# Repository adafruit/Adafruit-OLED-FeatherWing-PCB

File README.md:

## Adafruit FeatherWing OLED - 128x32 and 128x64 OLED Add-on For Feather PCB
<a href="http://www.adafruit.com/products/2900"><br/>
<a href="http://www.adafruit.com/products/2900"><br/>
Click here to purchase one from the Adafruit shop</a>

PCB files for the Adafruit FeatherWing OLED - 128x32 OLED Add-on For Feather. Format is EagleCAD schematic and board layout
* https://www.adafruit.com/product/2900

and for Adafruit FeatherWing OLED - 128x64 OLED Add-on For Feather - STEMMA QT / Qwiic
* https://www.adafruit.com/product/4650

### Description

A Feather board without ambition is a Feather board without FeatherWings! This is the **FeatherWing OLED**: it adds a 128x32 or 128x64 monochrome OLED plus 3 user buttons to any Feather main board. Using our [Feather Stacking Headers](https://www.adafruit.com/products/2830) or [Feather Female Headers](http://www.adafruit.com/products/2886) you can connect a FeatherWing on top of your Feather board and let the board take flight!

These displays are small, only about 1"-1.3" diagonal, but very readable due to the high contrast of an OLED display. This screen is made of 128x32 individual white OLED pixels and because the display makes its own light, no backlight is required. This reduces the power required to run the OLED and is why the display has such high contrast; we really like this miniature display for its crispness! We also toss on a reset button and three mini tactile buttons called A B and C so you can add a mini user interface to your feather.

The 128x64 display is an SH1107, which uses only I2C so you can easily connect it up with just two pins used (plus power and ground!).  There's an auto-reset circuit and a reset button on the top. We've even included a SparkFun qwiic-compatible STEMMA QT connector for the I2C bus so you can plug and play any of our STEMMA QT, qwiic or Grove I2C sensors and devices!

Tested working with **all Feather boards**. The OLED uses only the two I2C pins on the Feather, and you can pretty much stack it with any other FeatherWing, even ones that use I2C since that is a shared bus. To use, [Check out our tutorial ! It has schematics, datasheets, files, and code examples.](https://learn.adafruit.com/adafruit-oled-featherwing/download)

[Check out our range of Feather boards here.](https://www.adafruit.com/feather)

### License

Adafruit invests time and resources providing this open source design, please support Adafruit and open-source hardware by purchasing products from [Adafruit](https://www.adafruit.com)!

Designed by Limor Fried/Ladyada for Adafruit Industries.

Creative Commons Attribution/Share-Alike, all text above must be included in any redistribution. See license.txt for additional details.

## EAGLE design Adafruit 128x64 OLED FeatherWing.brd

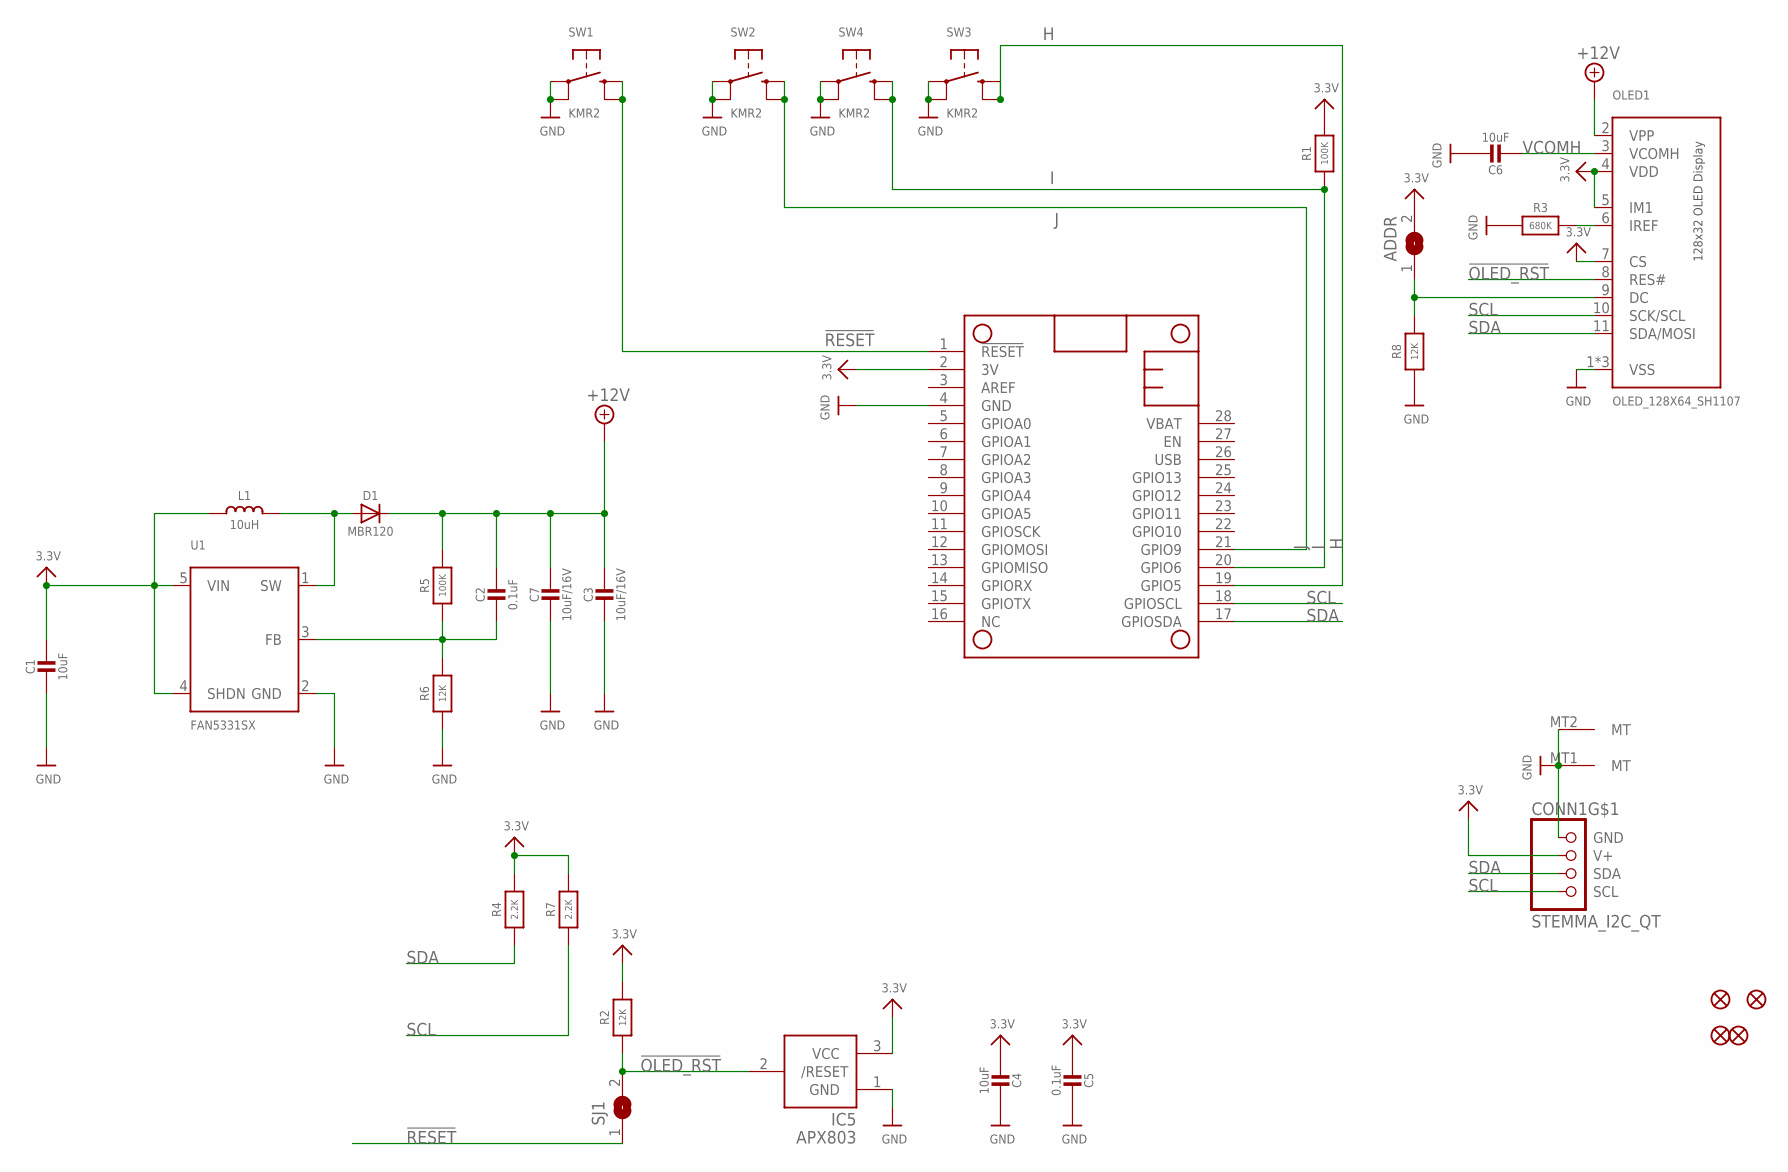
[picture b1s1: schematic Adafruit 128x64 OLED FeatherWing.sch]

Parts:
ADDR: SOLDERJUMPER; SOLDERJUMPER_ARROW_NOPASTE
C1, C4, C6: 10uF; 0805-NO
C2, C5: 0.1uF; 0603-NO
C3, C7: 10uF/16V; 0805-NO
CONN1: STEMMA_I2C_QT; JST_SH4
D1: MBR120; SOD-123
FID1, FID2, FID3, FID4: FIDUCIAL_1MM
IC5: APX803; SOT23
L1: 10uH; INDUCTOR_1007
MS1: FEATHERWING_NODIM
OLED1: OLED_128X64_SH1107; QT1107P11A
R1, R5: 100K; 0603-NO
R2, R6, R8: 12K; 0603-NO
R3: 680K; 0603-NO
R4, R7: 2.2K; 0603-NO
SJ1: SOLDERJUMPERCLOSED; SOLDERJUMPER_CLOSEDWIRE
SW1, SW2, SW3, SW4: KMR2; BTN_KMR2_4.6X2.8
U1: FAN5331SX; SOT23-5

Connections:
3.3V: ADDR.2, C1.1, C4.2, C5.2, CONN1.2 (V+), IC5.3 (VCC), L1.P$1 (1), MS1.2 (3V), OLED1.4 (VDD), OLED1.5 (IM1), OLED1.7 (CS), R1.2, R2.2, R4.2, R7.2, U1.4 (SHDN), U1.5 (VIN)
!OLED_RST: IC5.2 (/RESET), OLED1.8 (RES#), R2.1, SJ1.2
!RESET: MS1.1 (!RESET), SJ1.1, SW1.B (S), SW1.B' (S1)
+12V: C2.1, C3.1, C7.1, D1.C, OLED1.2 (VPP), R5.2
GND: C1.2, C3.2, C4.1, C5.1, C6.1, C7.2, CONN1.1 (GND), CONN1.MT1 (MT), CONN1.MT2 (MT), IC5.1 (GND), MS1.4 (GND), OLED1.1 (VSS), OLED1.12 (VSS), OLED1.13 (VSS), R3.1, R6.1, R8.1, SW1.A, SW1.A' (P1), SW2.A, SW2.A' (P1), SW3.A, SW3.A' (P1), SW4.A, SW4.A' (P1), U1.2 (GND)
H: MS1.19 (GPIO5), SW3.B (S), SW3.B' (S1)
I: MS1.20 (GPIO6), R1.1, SW4.B (S), SW4.B' (S1)
J: MS1.21 (GPIO9), SW2.B (S), SW2.B' (S1)
unnamed: D1.A, L1.P$2 (2), U1.1 (SW)
unnamed: ADDR.1, OLED1.9 (DC), R8.2
unnamed: C2.2, R5.1, R6.2, U1.3 (FB)
unnamed: OLED1.6 (IREF), R3.2
SCL: CONN1.4 (SCL), MS1.18 (GPIOSCL), OLED1.10 (SCK/SCL), R7.1
SDA: CONN1.3 (SDA), MS1.17 (GPIOSDA), OLED1.11 (SDA/MOSI), R4.1
VCOMH: C6.2, OLED1.3 (VCOMH)

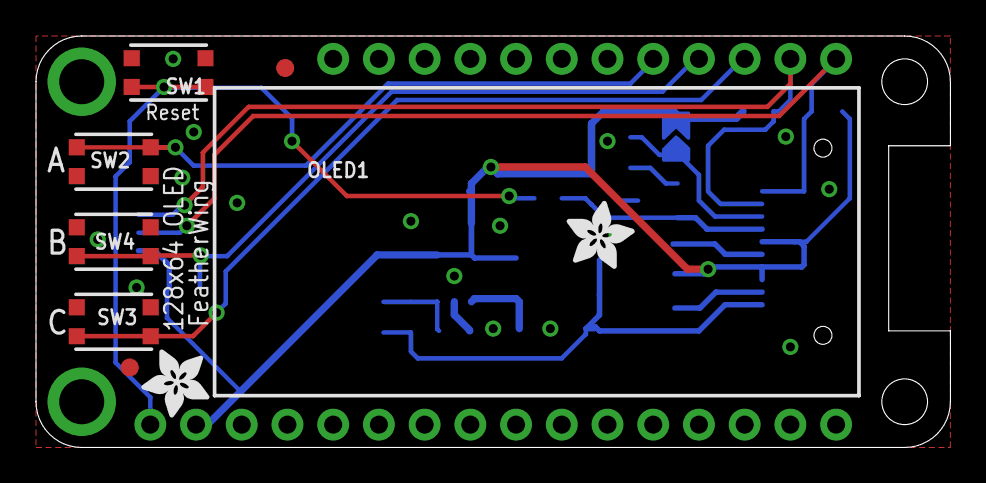
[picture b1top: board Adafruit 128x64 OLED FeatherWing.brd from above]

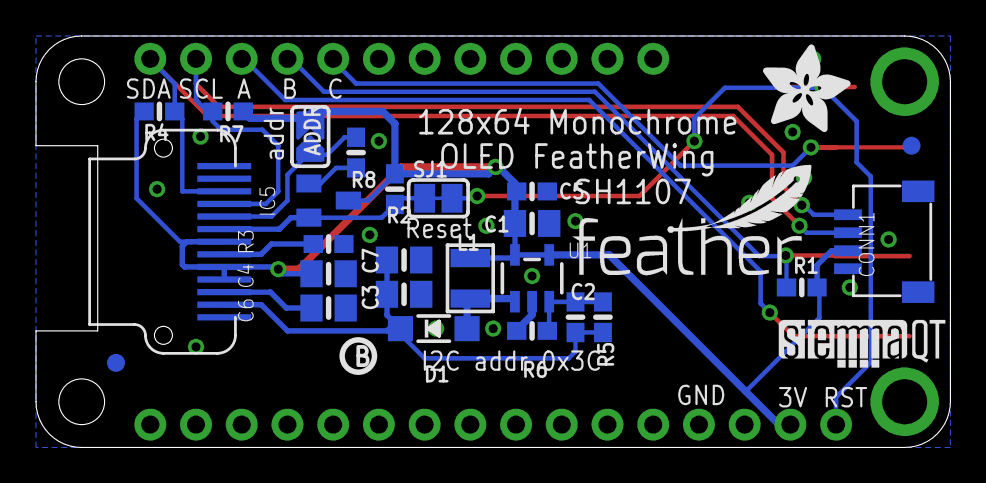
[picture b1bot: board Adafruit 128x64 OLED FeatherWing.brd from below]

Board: 2 copper layers, 50.8 x 22.9 mm, 38 parts (28 on the bottom side), 15 nets.

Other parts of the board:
U$8: ADAFRUIT_5MM
U$14: PCBFEAT-REV-040
U$16, U$37: ADAFRUIT_3.5MM
U$35: STEMMAQT
U$36: FEATHERLOGO_SMALL

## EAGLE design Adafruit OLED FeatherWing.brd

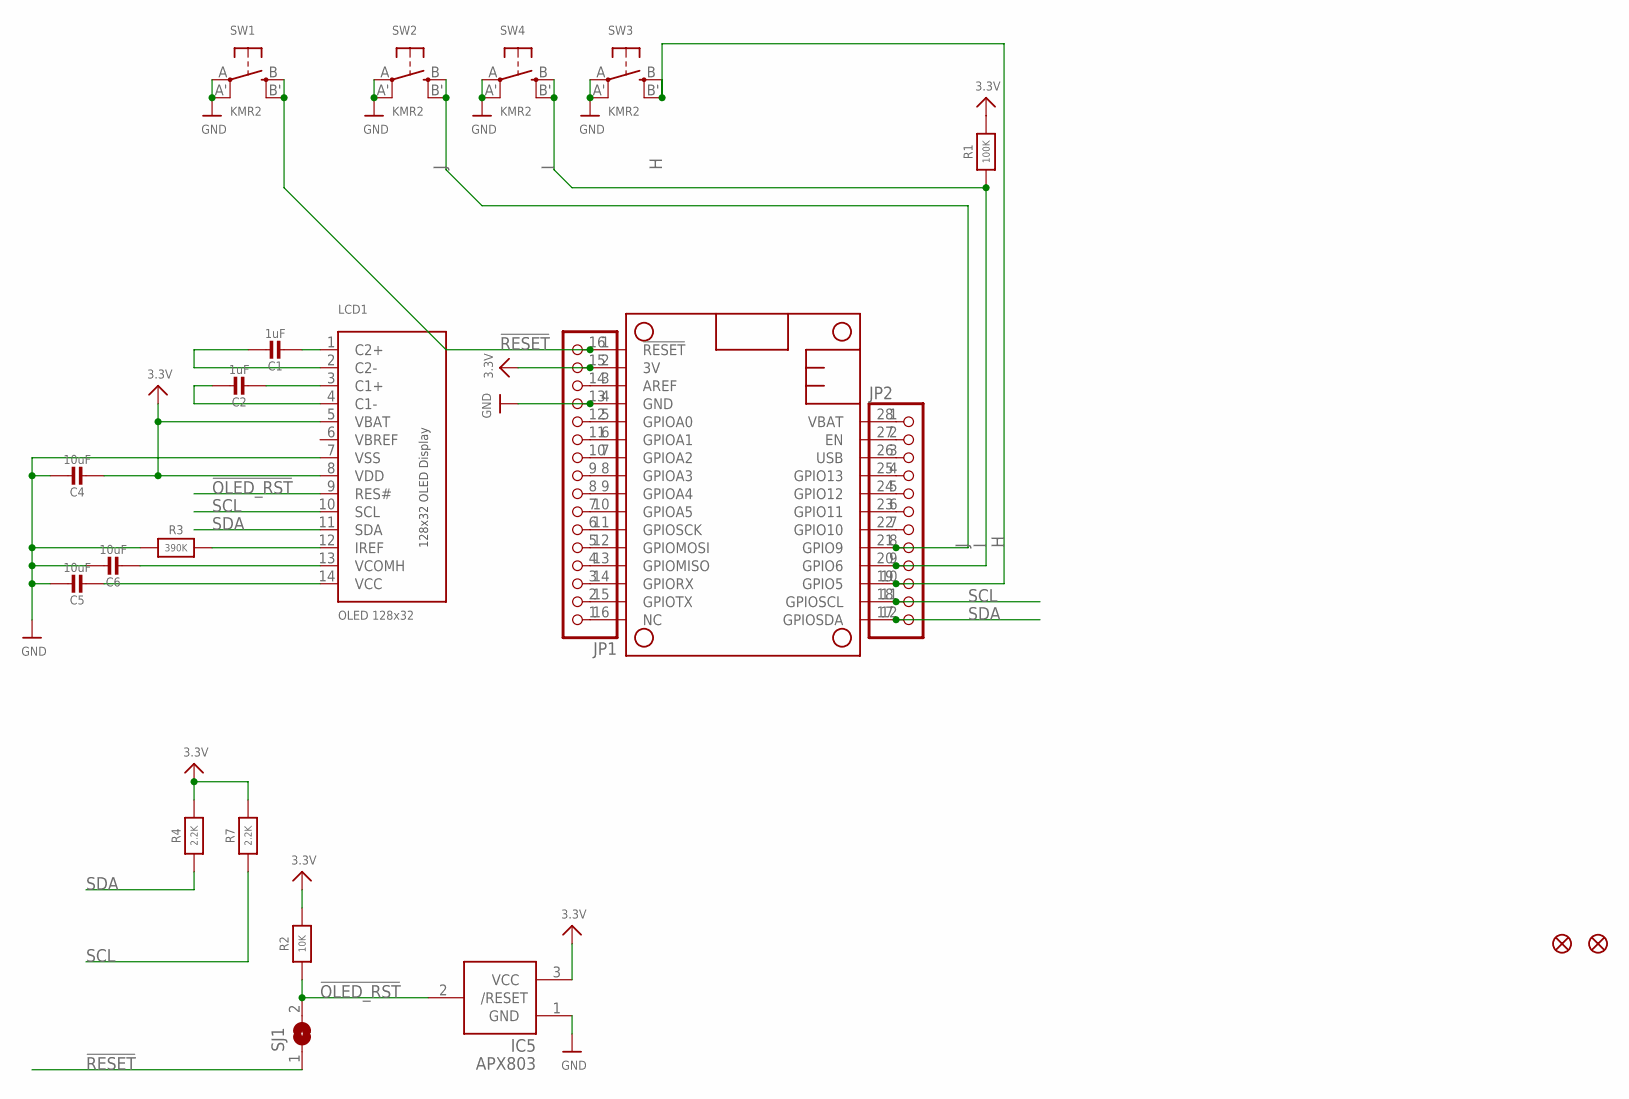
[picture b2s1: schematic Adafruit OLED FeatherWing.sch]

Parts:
C1, C2: 1uF; 0805-NO
C4, C5, C6: 10uF; 0805-NO
FID1, FID2: FIDUCIAL""; FIDUCIAL_1MM
IC5: APX803; SOT23
JP1: HEADER-1X16ROUND; 1X16_ROUND
JP2: HEADER-1X12; 1X12_ROUND
LCD1: OLED 128x32; UG-2832HSWEG02_WRAPUNDER
MS1: FEATHERWING
R1: 100K; 0805-NO
R2: 10K; _0805MP
R3: 390K; 0805-NO
R4, R7: 2.2K; 0805-NO
SJ1: SOLDERJUMPER; SOLDERJUMPER_ARROW_NOPASTE
SW1, SW2, SW3, SW4: KMR2; BTN_KMR2_4.6X2.8

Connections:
3.3V: C4.2, IC5.3 (VCC), JP1.15, LCD1.5 (VBAT), LCD1.8 (VDD), MS1.2 (3V), R1.2, R2.2, R4.2, R7.2
!OLED_RST: IC5.2 (/RESET), LCD1.9 (RES#), R2.1, SJ1.2
!RESET: JP1.16, MS1.1 (!RESET), SJ1.1, SW1.B (S), SW1.B' (S1)
A: JP1.12, MS1.5 (GPIOA0)
AREF: JP1.14, MS1.3 (AREF)
B: JP1.11, MS1.6 (GPIOA1)
C: JP1.10, MS1.7 (GPIOA2)
D: JP1.9, MS1.8 (GPIOA3)
E: JP1.8, MS1.9 (GPIOA4)
EN: JP2.2, MS1.27 (EN)
F: JP1.7, MS1.10 (GPIOA5)
G: JP1.1, MS1.16 (NC)
GND: C4.1, C5.1, C6.1, IC5.1 (GND), JP1.13, LCD1.7 (VSS), MS1.4 (GND), R3.1, SW1.A, SW1.A' (P1), SW2.A, SW2.A' (P1), SW3.A, SW3.A' (P1), SW4.A, SW4.A' (P1)
H: JP2.10, MS1.19 (GPIO5), SW3.B (S), SW3.B' (S1)
I: JP2.9, MS1.20 (GPIO6), R1.1, SW4.B (S), SW4.B' (S1)
J: JP2.8, MS1.21 (GPIO9), SW2.B (S), SW2.B' (S1)
K: JP2.7, MS1.22 (GPIO10)
L: JP2.6, MS1.23 (GPIO11)
M: JP2.5, MS1.24 (GPIO12)
MISO: JP1.4, MS1.13 (GPIOMISO)
MOSI: JP1.5, MS1.12 (GPIOMOSI)
N: JP2.4, MS1.25 (GPIO13)
unnamed: C1.2, LCD1.1 (C2+)
unnamed: C1.1, LCD1.2 (C2-)
unnamed: C2.2, LCD1.3 (C1+)
unnamed: C2.1, LCD1.4 (C1-)
unnamed: C6.2, LCD1.13 (VCOMH)
unnamed: C5.2, LCD1.14 (VCC)
unnamed: LCD1.12 (IREF), R3.2
RX: JP1.3, MS1.14 (GPIORX)
SCK: JP1.6, MS1.11 (GPIOSCK)
SCL: JP2.11, LCD1.10 (SCL), MS1.18 (GPIOSCL), R7.1
SDA: JP2.12, LCD1.11 (SDA), MS1.17 (GPIOSDA), R4.1
TX: JP1.2, MS1.15 (GPIOTX)
USB: JP2.3, MS1.26 (USB)
VBAT: JP2.1, MS1.28 (VBAT)
VBREF: LCD1.6 (VBREF)

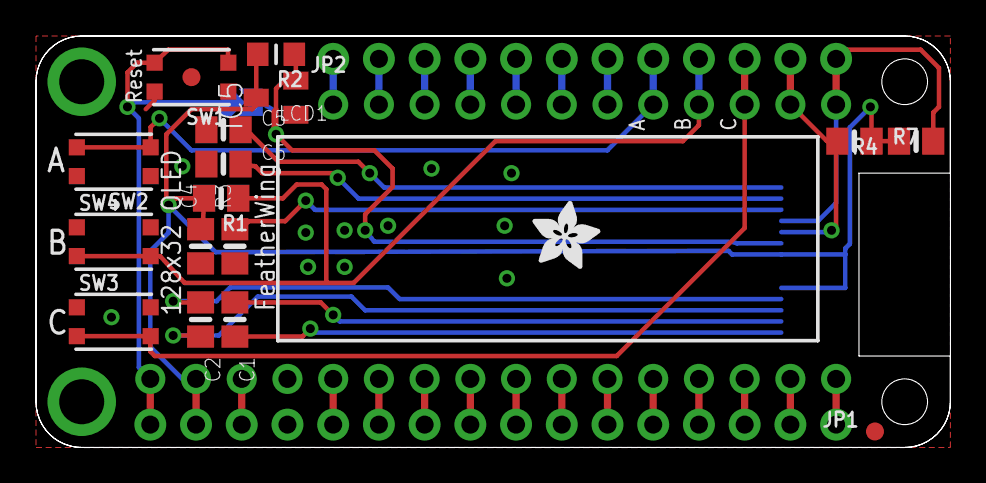
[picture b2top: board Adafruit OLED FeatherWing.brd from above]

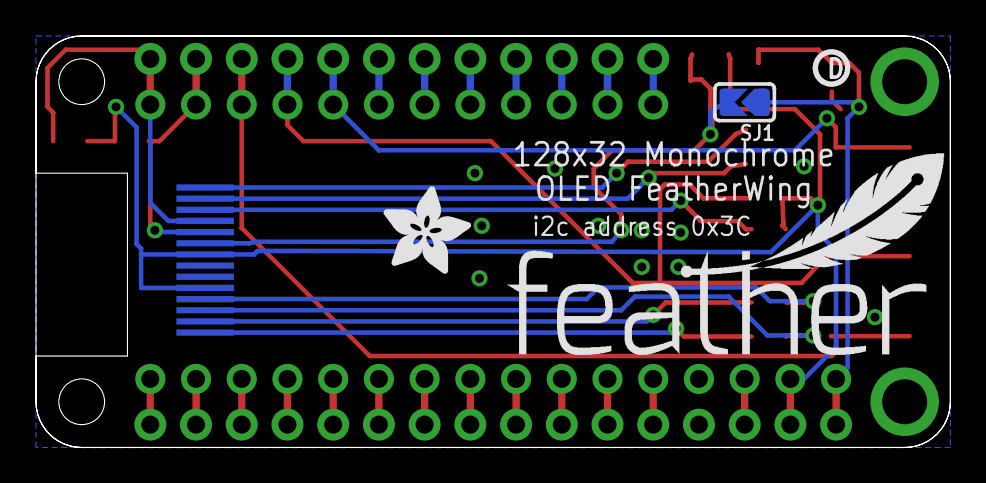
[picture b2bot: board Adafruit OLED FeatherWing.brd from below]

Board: 2 copper layers, 50.8 x 22.9 mm, 26 parts (4 on the bottom side), 36 nets.

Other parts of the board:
U$4: FEATHERLOGO
U$8: ADAFRUIT_5MM
U$14: PCBFEAT-REV-040
U$16: ADAFRUIT_3.5MM

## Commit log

2016-04-05 init
2019-02-15 Adding new PCB files.
2019-02-15 Removing old .brd file.
2019-02-15 removing old .sch file
2019-07-17 updated to use cookiecutter for pcb repos
2020-09-03 Add new board files.
2020-09-03 Add image asset.
